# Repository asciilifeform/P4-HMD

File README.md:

# Interface Board and Linux Support for Reflection Technology's "Private Eye P4" electromechanical HMD.

This project allows connecting the [Private Eye P4 head-mounted display](https://www.loper-os.org/?p=752) to an RPI-compatible Linux machine via an FPGA interface [board](/pcb/p4_pcb.png).

# You will need:

* The [Private Eye P4](/p4docs/p4.pdf) itself. (No, I don't know where you could get one. Sadly, it is entirely conceivable that I have the very last surviving unit.)
* An RPI or any similar machine with a compatible I/O pinout.
* [The interface PCB](/pcb/p4_schem.png) (I had 5 made for ~50 USD at JLC, but it's a 2-layer, so potentially hand-etchable. You will need the level shifter, passives, connectors (standard 2.54mm headers; as for the P4's data cable, the PCB footprint presumes [this](https://www.amazon.com/dp/B007PQ0ZG6) socket or its equivalent), and perhaps half an hour to solder.)
* A [TinyFPGA BX](https://www.crowdsupply.com/tinyfpga/tinyfpga-ax-bx) board (may be out of print now!) It is possible to use a different FPGA (you will need one with on-board SRAM) but then you will need to change certain things in the code, and, obviously, you will also need a different PCB.
* The code in this repo ([FPGA firmware](/fpga/) and [Linux kernel module](/kmod/).)

The display is 720x280 pixels but in fact natively rotated to 90 degrees, so it appears
as 280x720 to the hardware. The driver handles adjustable rotation, power management, brightness (1 bit!), RLE compression,
and differential updates. It may be used with xorg or in console mode. Refresh of the picture up to 30Hz is possible, though for small deltas it is in practice faster (we use run-length encoding in the FPGA and send only differences from the previous frame, when there was one.)

Animations look reasonable, and there is very little perceptible flicker, as the mirror actually vibrates at 50Hz, and at any given time, one entire 280-pixel column of the on-board framebuffer is always being displayed (rather than one pixel, and only during forward horizontal scan, as on e.g. a CRT refreshed at the same rate.) The 30Hz limit for full-frame updates comes from the maximum bit rate on the cable.

# Caution

**The Linux kernel module and its documentation was generated entirely using an LLM!** It runs stably (including when unit is unplugged and replugged) but could contain bugs! Including exploitable bugs! Use at your own risk.

# Possibly-interesting aspects

* LLM ("Claude Opus 4.5", "Max" variant) required ~2000 prompts to produce the Linux kernel module for this device.
* The [Linux kernel driver](/kmod/) makes correct use of DMA and does not substantially burden the CPU. It works with the current kernel, and can be used with very modest irons. Maximum SPI speed is limited to ~25MHz by the board's I/O impedance, but this is unimportant, as the maximum bit rate at which the P4 is able to receive differential picture updates is 8MHz. The FPGA performs the necessary buffering and clock domain crossing.
* There is support for [powering down/waking](/kmod/dpms.c) and [dimming/undimming](/kmod/backlight.c) the P4, as well as rotation.
* Display [rotation](/kmod/rotation.c) [uses NEON instructions where available](/kmod/rotate_neon.c). (Confirmed to work on RPI4.)
* [Vblank](https://www.chiark.greenend.org.uk/doc/linux-doc-3.16/html/drm/drm-vertical-blank.html) is [handled](/kmod/vblank.c)! 
* The [FPGA firmware](/fpga/) (hand-written, builds on [Yosys](https://github.com/YosysHQ/yosys)) includes a working fully-[asynchronous SPI slave controller](/fpga/spi_slave_async.v) for the [iCE40](https://www.latticesemi.com/en/Products/FPGAandCPLD/iCE40) -- an item AFAIK not previously published anywhere.
* The iCE40 is clocked at 16MHz and no PLL are used. However, the controller can receive just short of 16kB of buffer data in one shot at up to 100MHz (definitely not supported on RPI! and not particularly useful, but possible!) as the SPI slave and FIFO receiver are asynchronous! They are clocked with the host-supplied SPI clock, without any oversampling.
* The picture quality is not adequately represented by the above photo, as the P4 is a persistence-of-vision device (it contains a vibrating mirror and a column of 280 micro-LEDs.) The contrast ratio and sharpness (though not the resolution or colour depth!) are IMHO well ahead of today's OLED glasses, even though the P4 was released in 1990!
* The P4 originally included a CGA-compatible 8-bit ISA interface card (I threw mine out, as it did not appear to work reliably even with period hardware, or rather with any such as I was able to unearth.)
* The [vendor docs](/p4docs/p4.pdf) hint that horizontal resolutions in excess of 720 columns may be available (the 32kB SRAM framebuffer installed in the P4 suggests that this may be true: the official resolution 720x280 uses only 25200 bytes), but I have not been able to discover a means for setting any useful undocumented modes. Certain values of the reserved command bits do appear to produce a corrupted image where the swing of the mirror clearly exceeds what is seen when using the standard resolution. It is in fact possible to send a full 32kB to the P4 (any more and it crashes/resets) -- but the extra bits do not appear anywhere in the visible picture.

# More about the Private Eye

* [Vendor brochure.](/p4docs/Private_Eye_Brochure.pdf)
* [Collection of original vendor docs](https://www.eventhorizons.com/projects/P4/p4.html) where I found the interface data sheet.
* [Museum exhibit.](https://artsandculture.google.com/asset/reflection-technology-private-eye-display/QgFnZtDAdVz0CQ?hl=en)
* A [paper](https://sid.onlinelibrary.wiley.com/doi/full/10.1002/j.2637-496X.1990.tb05924.x) by the designers.
* [Photos of prototype.](https://www.virtual-boy.com/images/972309/)
* [Article](https://arstechnica.com/gaming/2024/05/virtual-boy-the-bizarre-rise-and-quick-fall-of-nintendos-enigmatic-red-console/) about the "Virtual Boy", Nintendo's attempt at integrating the Private Eye into a game console. Before I purchased my P4 in 2004, I had obtained and barbarically destroyed a "Virtual Boy" in a failed attempt to create a usable PC HMD (don't do this! they're valuable antiques now. And the HMD optics are not usable without the intact plastic chassis; and similarly, the driving chipset is not cleanly separable from the rest of the Virtual Boy.)
* [My ancient parallel port interface to the P4.](https://www.loper-os.org/vintage/paralleleye/eye.html)

# License

The driver: SPDX-License-Identifier: GPL-2.0

The FPGA code and PCB are public domain.

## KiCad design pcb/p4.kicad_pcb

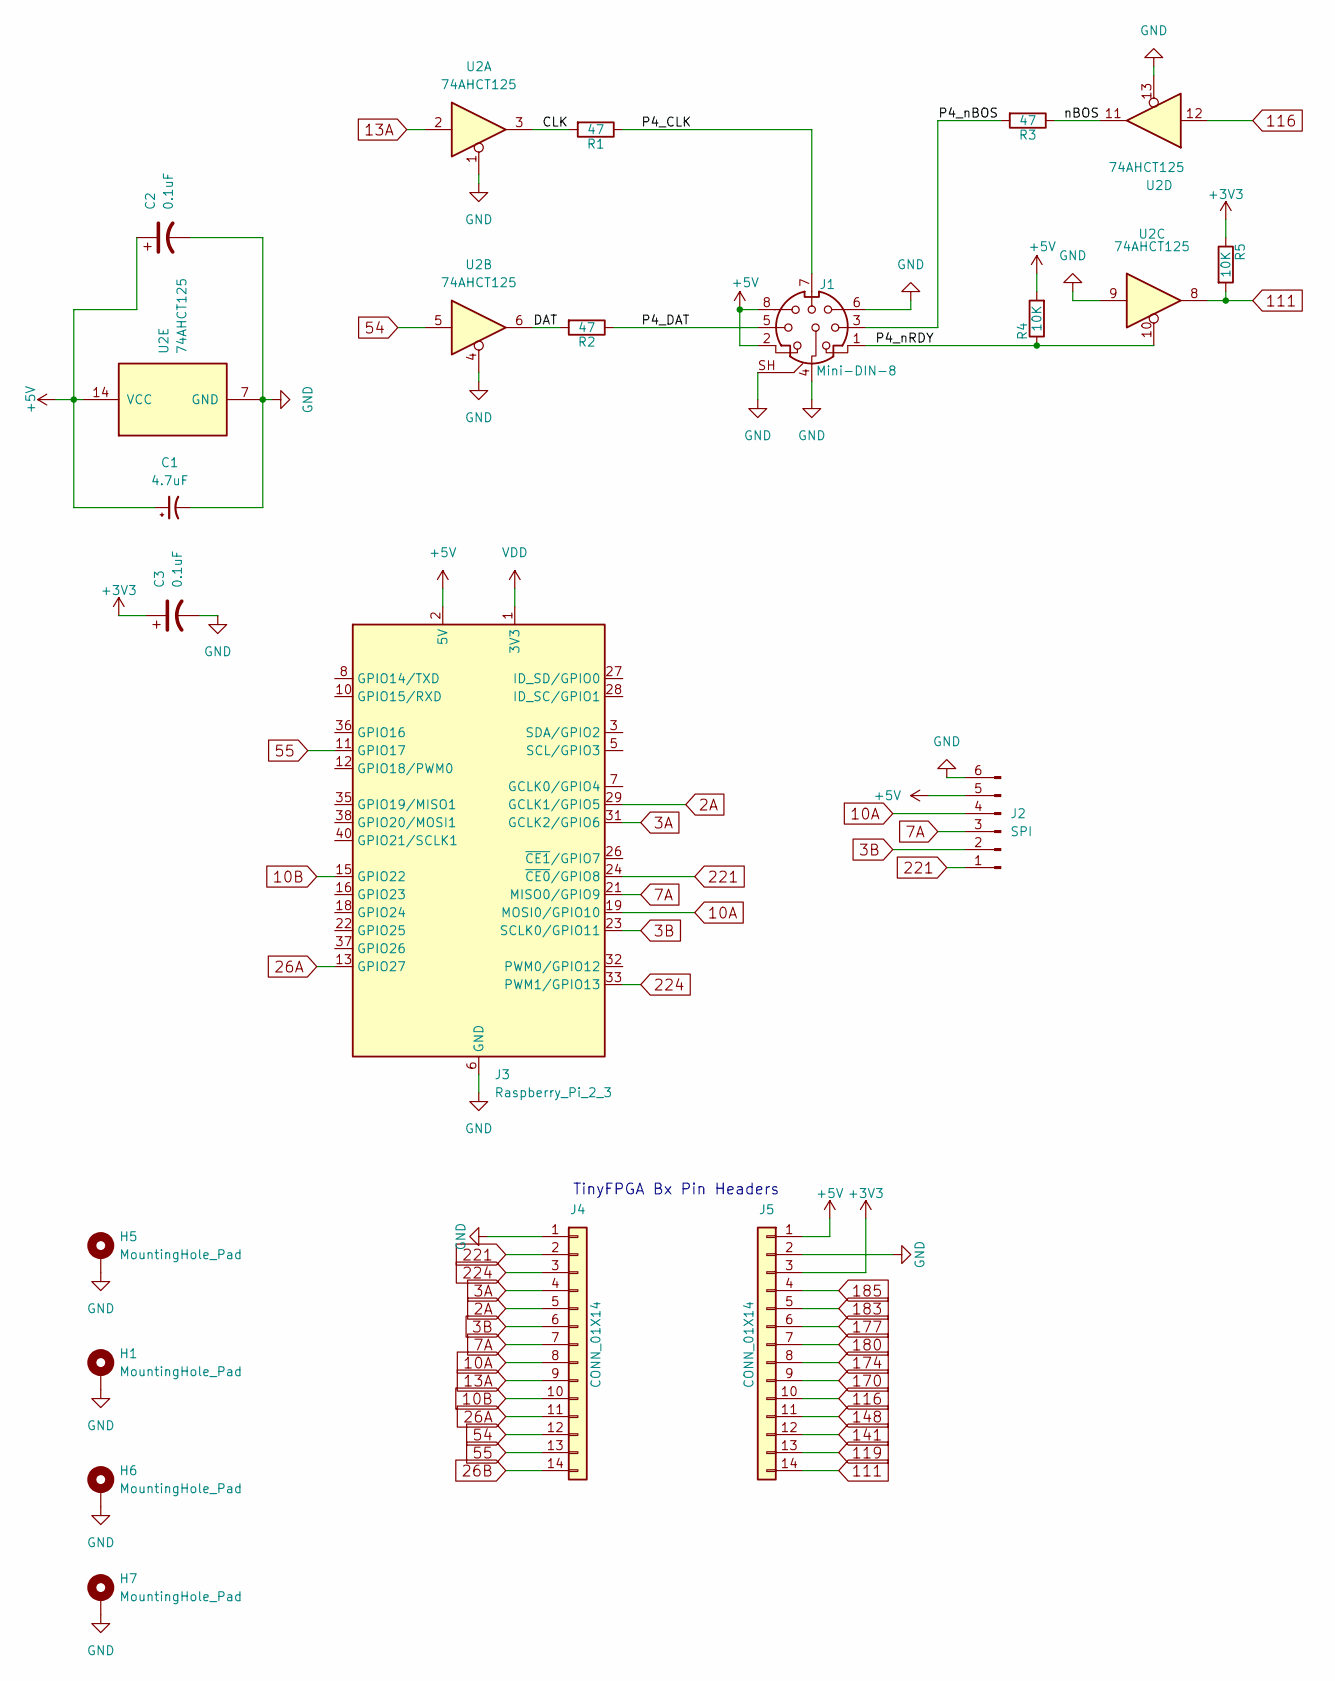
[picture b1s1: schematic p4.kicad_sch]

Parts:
C1: 4.7uF; CP_Radial_D5.0mm_P2.00mm
C2, C3: 0.1uF; C_Disc_D3.0mm_W1.6mm_P2.50mm
H1, H5, H6, H7: MountingHole_Pad; MountingHole_2.7mm_M2.5_DIN965_Pad
J1: Mini-DIN-8; Mini_DIN_round_8_canned
J2: SPI; PinHeader_1x06_P2.54mm_Vertical
J3: Raspberry_Pi_2_3; PinSocket_2x20_P2.54mm_Vertical
J4, J5: CONN_01X14; PinHeader_1x14_P2.54mm_Vertical
R1, R2, R3: 47; R_Axial_DIN0204_L3.6mm_D1.6mm_P7.62mm_Horizontal
R4, R5: 10K; R_Axial_DIN0204_L3.6mm_D1.6mm_P7.62mm_Horizontal
U2: 74AHCT125; DIP-14_W7.62mm

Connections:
2A: J3.29 (GCLK1/GPIO5), J4.5
3A: J3.31 (GCLK2/GPIO6), J4.4
3B: J2.2, J3.23 (SCLK0/GPIO11), J4.6
7A: J2.3, J3.21 (MISO0/GPIO9), J4.7
10A: J2.4, J3.19 (MOSI0/GPIO10), J4.8
10B: J3.15 (GPIO22), J4.10
13A: J4.9, U2.2
26A: J3.13 (GPIO27), J4.11
26B: J4.14
54: J4.12, U2.5
55: J3.11 (GPIO17), J4.13
111: J5.14, R5.2, U2.8
116: J5.10, U2.12
119: J5.13
141: J5.12
148: J5.11
170: J5.9
174: J5.8
177: J5.6
180: J5.7
183: J5.5
185: J5.4
221: J2.1, J3.24 (~CE0/GPIO8), J4.2
224: J3.33 (PWM1/GPIO13), J4.3
+3V3: C3.1, J5.3, R5.1
+5V: C1.1, C2.1, J1.2, J1.8, J2.5, J3.2 (5V), J3.4 (5V), J5.1, R4.2, U2.14 (VCC)
/CLK: R1.2, U2.3
/DAT: R2.2, U2.6
/P4_CLK: J1.7, R1.1
/P4_DAT: J1.5, R2.1
/P4_nBOS: J1.3, R3.2
/P4_nRDY: J1.1, R4.1, U2.10
/nBOS: R3.1, U2.11
GND: C1.2, C2.2, C3.2, H1.1, H5.1, H6.1, H7.1, J1.4, J1.6, J1.SH, J2.6, J3.6 (GND), J3.9 (GND), J3.14 (GND), J3.20 (GND), J3.25 (GND), J3.30 (GND), J3.34 (GND), J3.39 (GND), J4.1, J5.2, U2.1, U2.4, U2.7 (GND), U2.9, U2.13
VDD: J3.1 (3V3), J3.17 (3V3)

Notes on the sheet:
TinyFPGA Bx Pin Headers

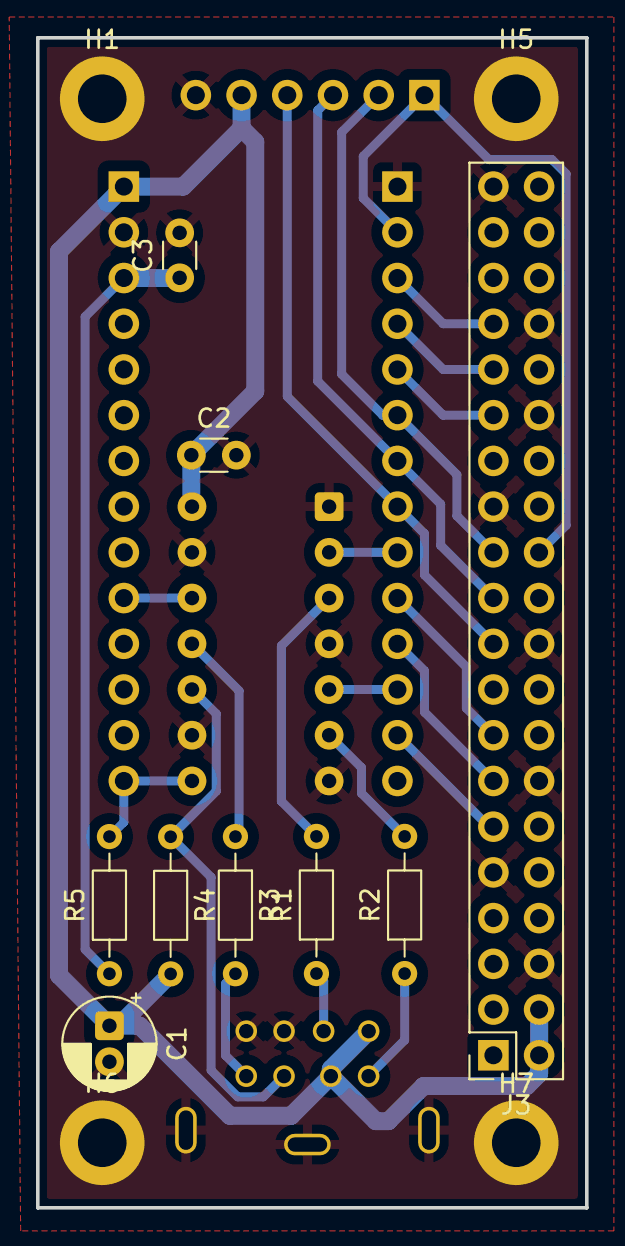
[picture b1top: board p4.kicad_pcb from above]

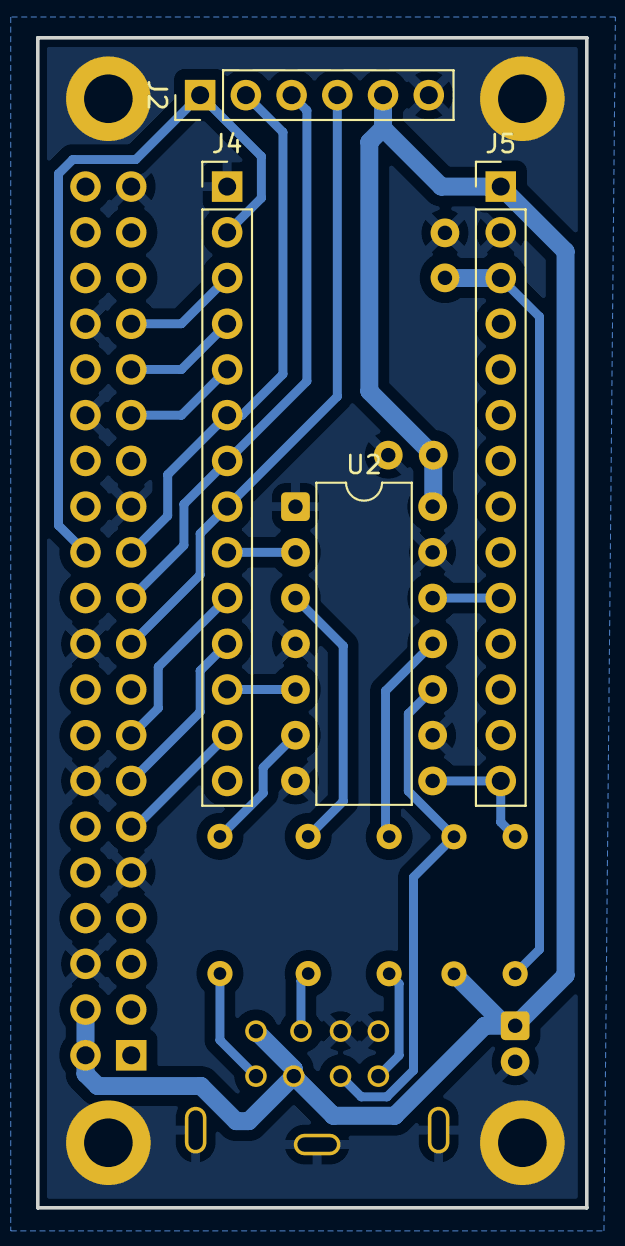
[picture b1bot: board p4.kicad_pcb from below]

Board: 2 copper layers, 30.5 x 65.0 mm, 18 parts (5 on the bottom side), 25 nets.

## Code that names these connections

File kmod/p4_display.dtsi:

// SPDX-License-Identifier: GPL-2.0
/*
 * Device Tree Overlay for P4 display on RPi SPI0
 * Generated from p4_pins.conf - do not edit directly
 * Regenerate with: make dtsi
 *
 * Compile:
 *   dtc -@ -I dts -O dtb -o p4_display.dtbo p4_display.dtsi
 *
 * Install:
 *   sudo cp p4_display.dtbo /boot/overlays/
 *
 * Enable in /boot/config.txt:
 *   dtoverlay=p4_display
 *
 * Pin Configuration:
 *   ENABLE  = GPIO5
 *   READY   = GPIO6
 *   COLD    = GPIO22
 *   NRESET  = GPIO13 (active low)
 *   NSLEEP  = GPIO17 (active low)
 *   VSYNC   = GPIO27
 */

/dts-v1/;
/plugin/;

/ {
	compatible = "brcm,bcm2711";

	/* Enable SPI0 */
	fragment@0 {
		target = <&spi0>;
		__overlay__ {
			status = "okay";
			#address-cells = <1>;
			#size-cells = <0>;

			/* Disable existing spidev@0 to free chipselect 0 */
			spidev@0 {
				status = "disabled";
			};

			p4_display: p4-display@0 {
				compatible = "example,p4-display";
				reg = <0>;  /* CE0 */
				spi-max-frequency = <28000000>;
				p4-overlay-id = "v130";
				/* SPI mode 0 (CPOL=0, CPHA=0) - no spi-cpol/spi-cpha */

				enable-gpios = <&gpio 5 0>;
				ready-gpios = <&gpio 6 0>;
				cold-gpios = <&gpio 22 0>;
				nreset-gpios = <&gpio 13 0>;  /* active-low HW, flag=0: driver uses physical values */
				nsleep-gpios = <&gpio 17 0>;  /* active-low HW, flag=0: driver uses physical values */
				vsync-gpios = <&gpio 27 0>;

				/* upside-down; */  /* Uncomment for 180° flip at boot */
			};
		};
	};

	/* Configure GPIO pin modes */
	fragment@1 {
		target = <&gpio>;
		__overlay__ {
			p4_pins: p4_pins {
				brcm,pins = <5 6 22 13 17 27>;
				brcm,function = <1 0 0 1 1 0>;  /* out, in, in, out, out, in */
				brcm,pull = <0 0 0 0 0 0>;      /* none */
			};
		};
	};

	/* Parameters for runtime customization */
	__overrides__ {
		speed = <&p4_display>, "spi-max-frequency:0";
		enable_pin = <&p4_display>, "enable-gpios:4";
		ready_pin = <&p4_display>, "ready-gpios:4";
		cold_pin = <&p4_display>, "cold-gpios:4";
		nreset_pin = <&p4_display>, "nreset-gpios:4";
		nsleep_pin = <&p4_display>, "nsleep-gpios:4";
		vsync_pin = <&p4_display>, "vsync-gpios:4";
	};
};

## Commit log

2026-02-27 First publication.
2026-02-27 Reduce photos.
2026-02-27 Revise README for Private Eye P4 interface board
    Updated project title and added images to README.
2026-02-27 Update README to clarify bot-generated content
    Added a warning about bot-generated content in the README.
2026-02-27 Add 'Possibly Interesting Aspects' section to README
    Added section on possibly interesting aspects of the project, including details about LLM prompts and FPGA code.
2026-02-27 Include the ancient datasheet for the P4.
2026-02-27 Update README with additional requirements
2026-02-27 Improve README links for interface PCB and code
    Updated links in the requirements section for clarity.
2026-02-27 Update README with P4 interface card details
    Added information about the P4's ISA interface card and undocumented modes.
2026-02-27 Update README with display and driver information
    Clarified display rotation and added details about driver features and performance.
2026-02-27 Enhance P4 features description in README
    Updated the description of P4 features to include support for dimming and rotation.
2026-02-27 Add Vblank handling information to README
2026-02-27 Clarify vendor docs statement about horizontal resolutions
2026-02-27 Enhance README with iCE40 SPI controller details
    Added details about the iCE40 clock speed and buffer data capabilities.
2026-02-28 Update README with additional P4 resolution details
    Clarify details about the P4's capabilities and limitations regarding horizontal resolutions and framebuffer usage.
2026-02-28 Enhance README with detailed driver and FPGA info
    Updated README to include detailed descriptions of the Linux kernel driver, power management, display rotation, and FPGA firmware functionalities.
2026-02-28 Update README with detailed PCB and connector info
    Clarified details about the interface PCB and connector specifications.
2026-02-28 Add more info section for the Private Eye
    Added additional resources and links related to the Private Eye.
2026-02-28 Update section header for Private Eye information
2026-02-28 Update README formatting and content clarity
2026-02-28 Add public domain notice for FPGA code and PCB
2026-02-28 Update vendor brochure link in README
2026-02-28 Clarify interface board and FPGA requirements in README
    Updated README to clarify the interface board and TinyFPGA BX requirements.
2026-02-28 Fix formatting issue in README.md
2026-02-28 Enhance README with animation and flicker details
    Added details about animation performance and flicker reduction.
2026-02-28 Add images for optics and vendor in README
    Added images to README for better visual representation.
2026-03-01 Update README for clarity on pixel column display
    Clarified the description of pixel column visibility in animations.
2026-03-02 Improve README animation description
    Clarified description of display refresh rate and framebuffer visibility.
